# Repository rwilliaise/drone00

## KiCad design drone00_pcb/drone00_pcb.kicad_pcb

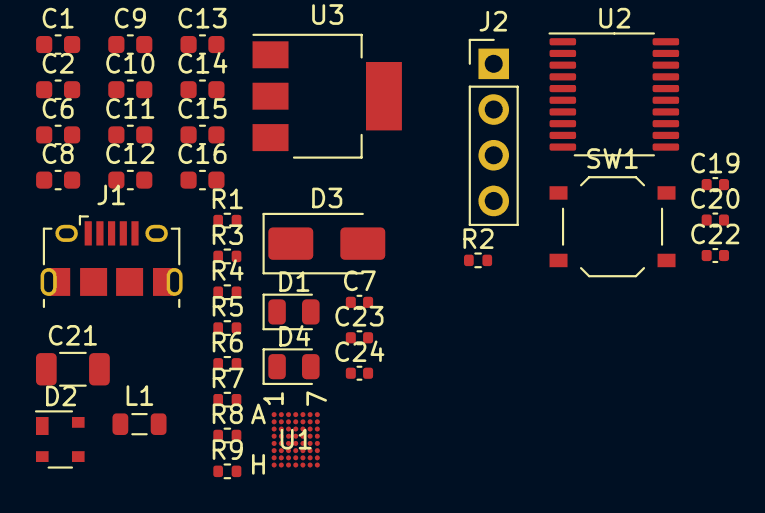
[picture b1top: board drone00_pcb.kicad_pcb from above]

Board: 2 copper layers, 39 parts (0 on the bottom side), 26 nets, no tracks yet.

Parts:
C1, C6: 47n; C_0603_1608Metric
C2, C8, C16: 100n; C_0603_1608Metric
C7: 1n; C_0402_1005Metric
C9, C10, C11, C12, C13, C14, C15: 10u; C_0603_1608Metric
C19, C23, C24: 1u; C_0402_1005Metric
C20, C22: 100n; C_0402_1005Metric
C21: 1n; C_1206_3216Metric
D1: YELLOW; LED_0805_2012Metric
D2: PRTR5V0U2X; SOT-143
D3: SS14; D_SMA
D4: GREEN; LED_0805_2012Metric
J1: USB_B_Micro; USB_Micro-B_Amphenol_10118194_Horizontal
J2: STLINK; PinHeader_1x04_P2.54mm_Vertical
L1: 1u; L_0805_2012Metric
R1: 1M; R_0402_1005Metric
R2: 10k; R_0402_1005Metric
R3: 2.2k; R_0402_1005Metric
R4, R5: 100k; R_0402_1005Metric
R6: 17.4k; R_0402_1005Metric
R7, R8: 100; R_0402_1005Metric
R9: 330; R_0402_1005Metric
SW1: RESET; SW_Push_1P1T_XKB_TS-1187A
U1: BQ24179YBGR; BGA_79YBGR_TEX
U2: STM8S003F3P; TSSOP-20_4.4x6.5mm_P0.65mm
U3: AMS1117-3.3; SOT-223-3_TabPin2

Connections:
+3V3: C23.1, R9.1, U3.2 (VO)
+5V: C20.1, C24.1, D3.1 (K), J2.4, R2.2, U2.9 (VDD), U3.3 (VI)
/controller/SWIM: J2.3, U2.18 (PD1)
/power/BATP: C14.2, C15.2, R8.2, U1.A7 (BAT), U1.B7 (BAT), U1.C7 (BAT), U1.D7 (BAT), U1.E7 (BAT)
/power/ILIM_HIZ: R4.2, R5.1, U1.F4 (ILIM_HIZ)
/power/REGN: R3.1, R4.1, U1.E1 (REGN)
GND: C2.1, C7.1, C8.1, C9.1, C10.1, C11.1, C12.1, C13.1, C14.1, C15.1, C16.2, C19.1, C20.2, C21.2, C22.1, C23.2, C24.2, D4.1 (K), J1.5 (GND), J2.2, R1.2, R5.2, R6.1, R7.2, SW1.1, U1.A4 (GND), U1.B4 (GND), U1.C4 (GND), U1.D4 (GND), U1.E4 (GND), U1.G2 (ACDRV2), U1.H2 (ACDRV1), U2.7 (VSS), U3.1 (GND)
unnamed: C1.1, L1.1, U1.A3 (SW1), U1.B3 (SW1), U1.C3 (SW1), U1.D3 (SW1), U1.E3 (SW1)
unnamed: C2.2, U1.A2 (PMID), U1.B2 (PMID), U1.C2 (PMID), U1.D2 (PMID), U1.E2 (PMID)
unnamed: C6.1, L1.2, U1.A5 (SW2), U1.B5 (SW2), U1.C5 (SW2), U1.D5 (SW2), U1.E5 (SW2)
unnamed: D1.2 (A), R3.2
unnamed: D1.1 (K), U1.F1 (STAT)
unnamed: C21.1, D2.1 (GND), J1.6 (Shield), R1.1
unnamed: D2.2 (I/O1), J1.3 (D+), U1.F2 (D+)
unnamed: D2.3 (I/O2), J1.2 (D-), U1.F3 (D-)
unnamed: D4.2 (A), R9.2
unnamed: C22.2, J2.1, R2.1, SW1.2, U2.4 (NRST)
unnamed: R7.1, U1.G6 (BATN)
unnamed: R8.1, U1.G7 (BATP)
unnamed: C1.2, U1.D1 (BTST1)
unnamed: C6.2, U1.F7 (BTST2)
unnamed: R6.2, U1.F5 (PROG)
unnamed: C7.2, U1.F6 (SDRV)
unnamed: C19.2, U2.8 (VCAP)
SYS: C8.2, C9.2, C10.2, C11.2, C12.2, C13.2, U1.A6 (SYS), U1.B6 (SYS), U1.C6 (SYS), U1.D6 (SYS), U1.E6 (SYS)
VBUS: C16.1, D2.4 (VCC), D3.2 (A), J1.1 (VBUS), U1.A1 (VBUS), U1.B1 (VBUS), U1.C1 (VBUS), U1.G1 (VAC2), U1.H1 (VAC1)

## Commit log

2024-03-09 Create LICENSE
2024-03-14 Add BQ24
2024-03-15 Finish footprints
